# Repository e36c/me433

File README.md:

# me433
Repository for my work in ME433.

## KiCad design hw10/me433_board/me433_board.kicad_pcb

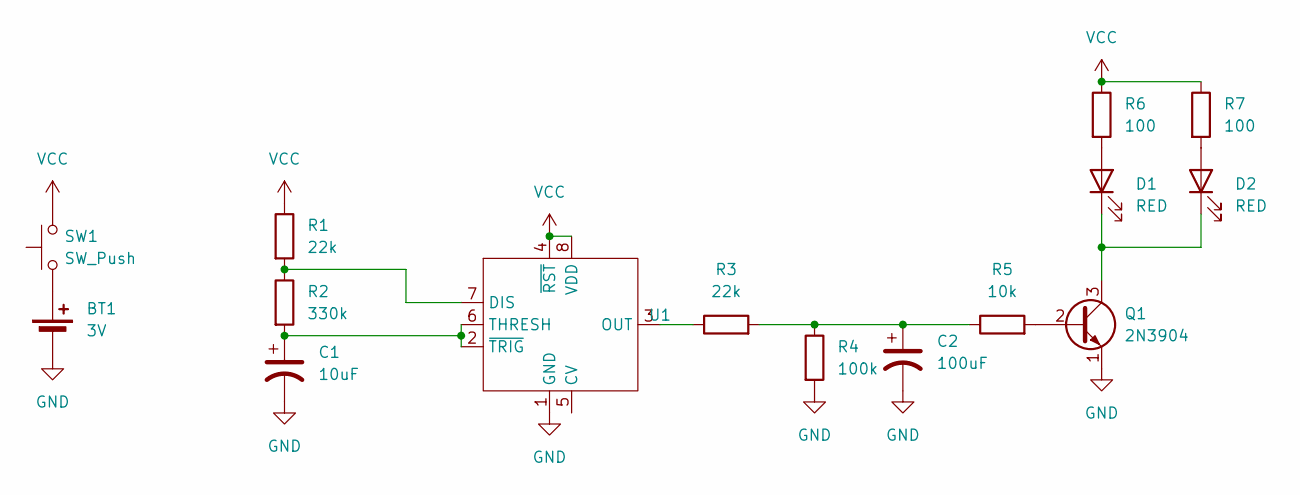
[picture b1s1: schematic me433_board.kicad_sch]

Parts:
BT1: 3V; BatteryHolder_Keystone_103_1x20mm
C1: 10uF; CP_Radial_D8.0mm_P3.50mm
C2: 100uF; CP_Radial_D10.0mm_P3.80mm
D1, D2: RED; LED_0805_2012Metric
Q1: 2N3904; TO-92_Inline
R1, R3: 22k; R_0805_2012Metric
R2: 330k; R_0805_2012Metric
R4: 100k; R_0805_2012Metric
R5: 10k; R_0805_2012Metric
R6, R7: 100; R_0805_2012Metric
SW1: SW_Push; SW_DIP_SPSTx01_Slide_Copal_CHS-01A_W5.08mm_P1.27mm_JPin
U1: ICM7555-PDIP

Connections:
GND: BT1.2 (-), C1.2, C2.2, Q1.1 (E), R4.2, U1.1 (GND)
unnamed: BT1.1 (+), SW1.1
unnamed: C2.1, R3.2, R4.1, R5.1
unnamed: D1.2 (A), R6.2
unnamed: D1.1 (K), D2.1 (K), Q1.3 (C)
unnamed: D2.2 (A), R7.2
unnamed: Q1.2 (B), R5.2
unnamed: R1.2, R2.1, U1.7 (DIS)
unnamed: R3.1, U1.3 (OUT)
unnamed: C1.1, R2.2, U1.2 (~TRIG), U1.6 (THRESH)
VCC: R1.1, R6.1, R7.1, SW1.2, U1.4 (~RST), U1.8 (VDD)

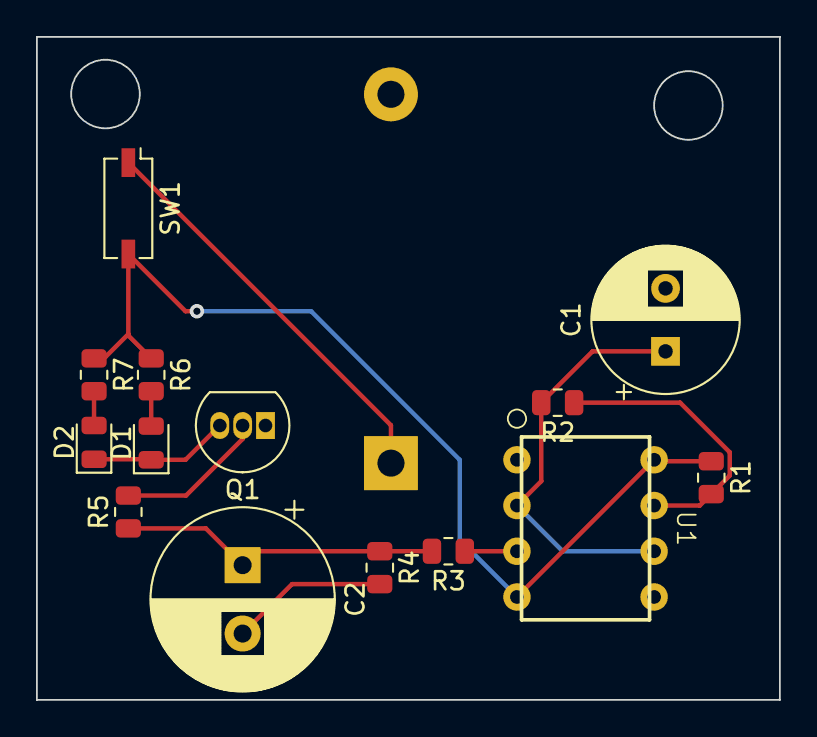
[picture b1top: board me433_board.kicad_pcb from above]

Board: 2 copper layers, 41.3 x 36.8 mm, 15 parts (1 on the bottom side), 11 nets.

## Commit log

2024-04-01 Created blink.c and added video demo.
2024-04-15 Completed HW3
    Configured CMake after much struggle and completed HW3.
2024-04-15 Deleted build in root folder
    For some reason there was a 'build' folder in the main path - it is deleted
2024-04-15 Actually completed HW3
    Turns out the 'build' folder in the root directory is required. Corrected button press part of HW3 and added demo.mov
2024-04-22 Completed HW4
    Completed HW4 and made demo video.
2024-05-04 Completed HW6
    Added folder for HW6 copying files from previous homeworks, then completed it.
2024-05-04 Added demo video
2024-05-12 Completed HW7
    Created and finished HW7, including demo video.
2024-05-22 Completed HW16
    Completed HW16 and took demo video.
2024-05-23 Completed HW12
    Completed HW12 and took demo video.
2024-05-29 Completed HW9
    Completed HW9 and added demo video. Also began HW15 -- about halfway through.
2024-05-29 Completed HW15
    Created all models for HW15. .SLDPRT and .jpg of each are included.
2024-06-03 Completed HW10
    Completed HW10, along with screenshots of schematic and PCB.
2024-06-04 Completed HW14
    Completed HW14.
2024-06-04 Completed ME433
    Completed HW5 to officially finish ME433.
